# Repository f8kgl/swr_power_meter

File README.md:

# swr_power_meter
Repo of Swr Power Meter project of F8KGL

Afin d'optimiser la qualité de ses communications, l'OM cherche à rendre maximum le transfert de puissance entre l’antenne et l’émetteur (et vice et versa). Ce point de fonctionnement optimum est atteint lorsque les impédances entre l’antenne et l’émetteur sont « adaptées ». Alors, la puissance réfléchie est minimale (idéalement nulle), ou le « SWR » (ou ROS), pour « Standing Wave Ratio » (ou Rapport d’Onde Stationnaire) est proche de (idéalement égal à) 1.

Le « SWR Power Meter F8KGL » (ou Wattmètre/ROSmètre F8KGL) est un dispositif permettant de mesurer la puissance transmise à l’antenne, la puissance réfléchie, et le « SWR ». Il donne ainsi la mesure de la qualité de la chaîne de transmission TRX/Antenne.

Le « SWR Power Meter F8KGL » doit répondre aux besoins suivants :

	-mesurer une puissance de 1W à 500W, avec une précision de 10 %
	-mesurer une puissance dans les 3 bandes radioamateurs HF, VHF, UHF
	-être utilisable par une grande majorité des TRX radioamateurs (50 Ω)
	-être alimenté par une source extérieure en 13,8V, ou par un pack batterie 4x1,5V LR6
	-atténuer le moins possible le signal à transmettre (max 0,2dB)
	-afficher le résultat de la mesure sur un écran LCD (puissance en W, et le SWR sans unité)
	-être solide et robuste pour une utilisation en contest et /P
	-être vendable sous la forme de kit

Ces besoins ont été définis par l’état de l’art technique actuel. En particulier, la technologie moderne appelle l’utilisation de l’électronique numérique le plus souvent possible. C’est pourquoi, l’affichage sur un écran LCD a été choisi. De plus, l’utilisation de moyens informatiques, aussi simples et modestes soient-ils, est préconisé. C’est pourquoi, un microcontrôleur a été choisi pour faire l’interface entre la mesure et l’affichage.

Ce dispositif a été conçu par les OM du club radioamateur « Vauréal Amitié Radio », situé à Vauréal (95), sous l’indicatif F8KGL.
Le projet a été développé par André F0EOS, et Fabrice F4BJH. Portons également à l’attention du lecteur, que l’idée initiale vient de Pierre F1FDD.

1/GPUTILS

1.1/ Désinstaller la version courante de la distribution  
1.2/ Télécharger la version 1.5.0-1 en suivant ce lien :  
https://sourceforge.net/projects/gputils/files/gputils/1.5.0/gputils-1.5.0-1.tar.gz/download  
1.3/ Installation  

	$ tar -xvzf gputils-1.5.0-1.tar.gz

	$ cd gputils-1.5.0-1.tar.gz

	$ ./configure

	$make

	$sudo make install

2/GPSIM  
2.1/ Désinstaller la version courante de la distribution  
2.2/ Télécharger la version 0.31.0 en suivant ce lien :  
https://sourceforge.net/projects/gpsim/files/gpsim/0.31.0/  
2.3/ Installation  

	$tar -xvzf gpsim-0.31.0.tar.gz

	$cd gpsim-0.31.0/

	$./configure

	$make

	$sudo make install

	$sudo /sbin/ldconfig

2.4/Librairie et module GPSIM  
2.4.1/ Création de lien symboliques vers les sources de la librairie, des modules, et le Makefile  

		$cd .../gpsim0.31/modules   #répertoire ou gpsim a été dézippé

		$ ln -s .../swr_power_meter/src/hw/sim/gpsim/lib/Makefile.am

		$ ln -s .../swr_power_meter/src/hw/sim/gpsim/lib/ltc2305.cc

		$ ln -s .../swr_power_meter/src/hw/sim/gpsim/lib/ltc2305.h

		$ ln -s .../swr_power_meter/src/hw/sim/gpsim/lib/swrpowermeterf8kgl_modules.cc

2.4.2/ compiler les fichiers ajoutés  

		$cd .../gpsim0.31/ #répertoire ou gpsim a été dézippé

		$ autoreconf

		$./configure

		$make

		$sudo make install

		$sudo /sbin/ldconfig

3/Utilisation du projet swr_power_meter_f8kgl  
3.1/Télécharger le projet : git clone https://github.com/f8kgl/swr_power_meter  
	$ cd .../prj
	$ make test

	$ cd .../prj
	$ make calibration 

3.2/Calibrator  
    $ cd .../prj  
    $ make calibration_gpsim  

	le make génère le fichier .hex de calibration, à flasher dans l'EEPROM du PIC  

	Usage :
	calibrator [-o][-t][-f][-r][-a adc_value][-p P_in]
	-o : calibration pour le fw opérationnel
	-t : calibration pour le fw de test
	-f : Port FWD
	-r : Port REF
	-a : valeur d'ADC (ADC_m)
	-p : Valeur de puissance en W (Pfwd)

3.3/Simulation  
3.3.1/Modifier le fichier prj/swr_power_meter.stc pour utiliser le fichier de calibration généré à l'étape précédente. Effecteur la mise à jour du projet gpsim :  

   $ cd .../prj
	 $ make update_gpsim

3.3.2/ Lancement de gpsim  
 $ cd .../bin
 $ gpsim -c swr_power_meter.stc

 $ gpsim -c <hardware>.CALIBRATION.stc

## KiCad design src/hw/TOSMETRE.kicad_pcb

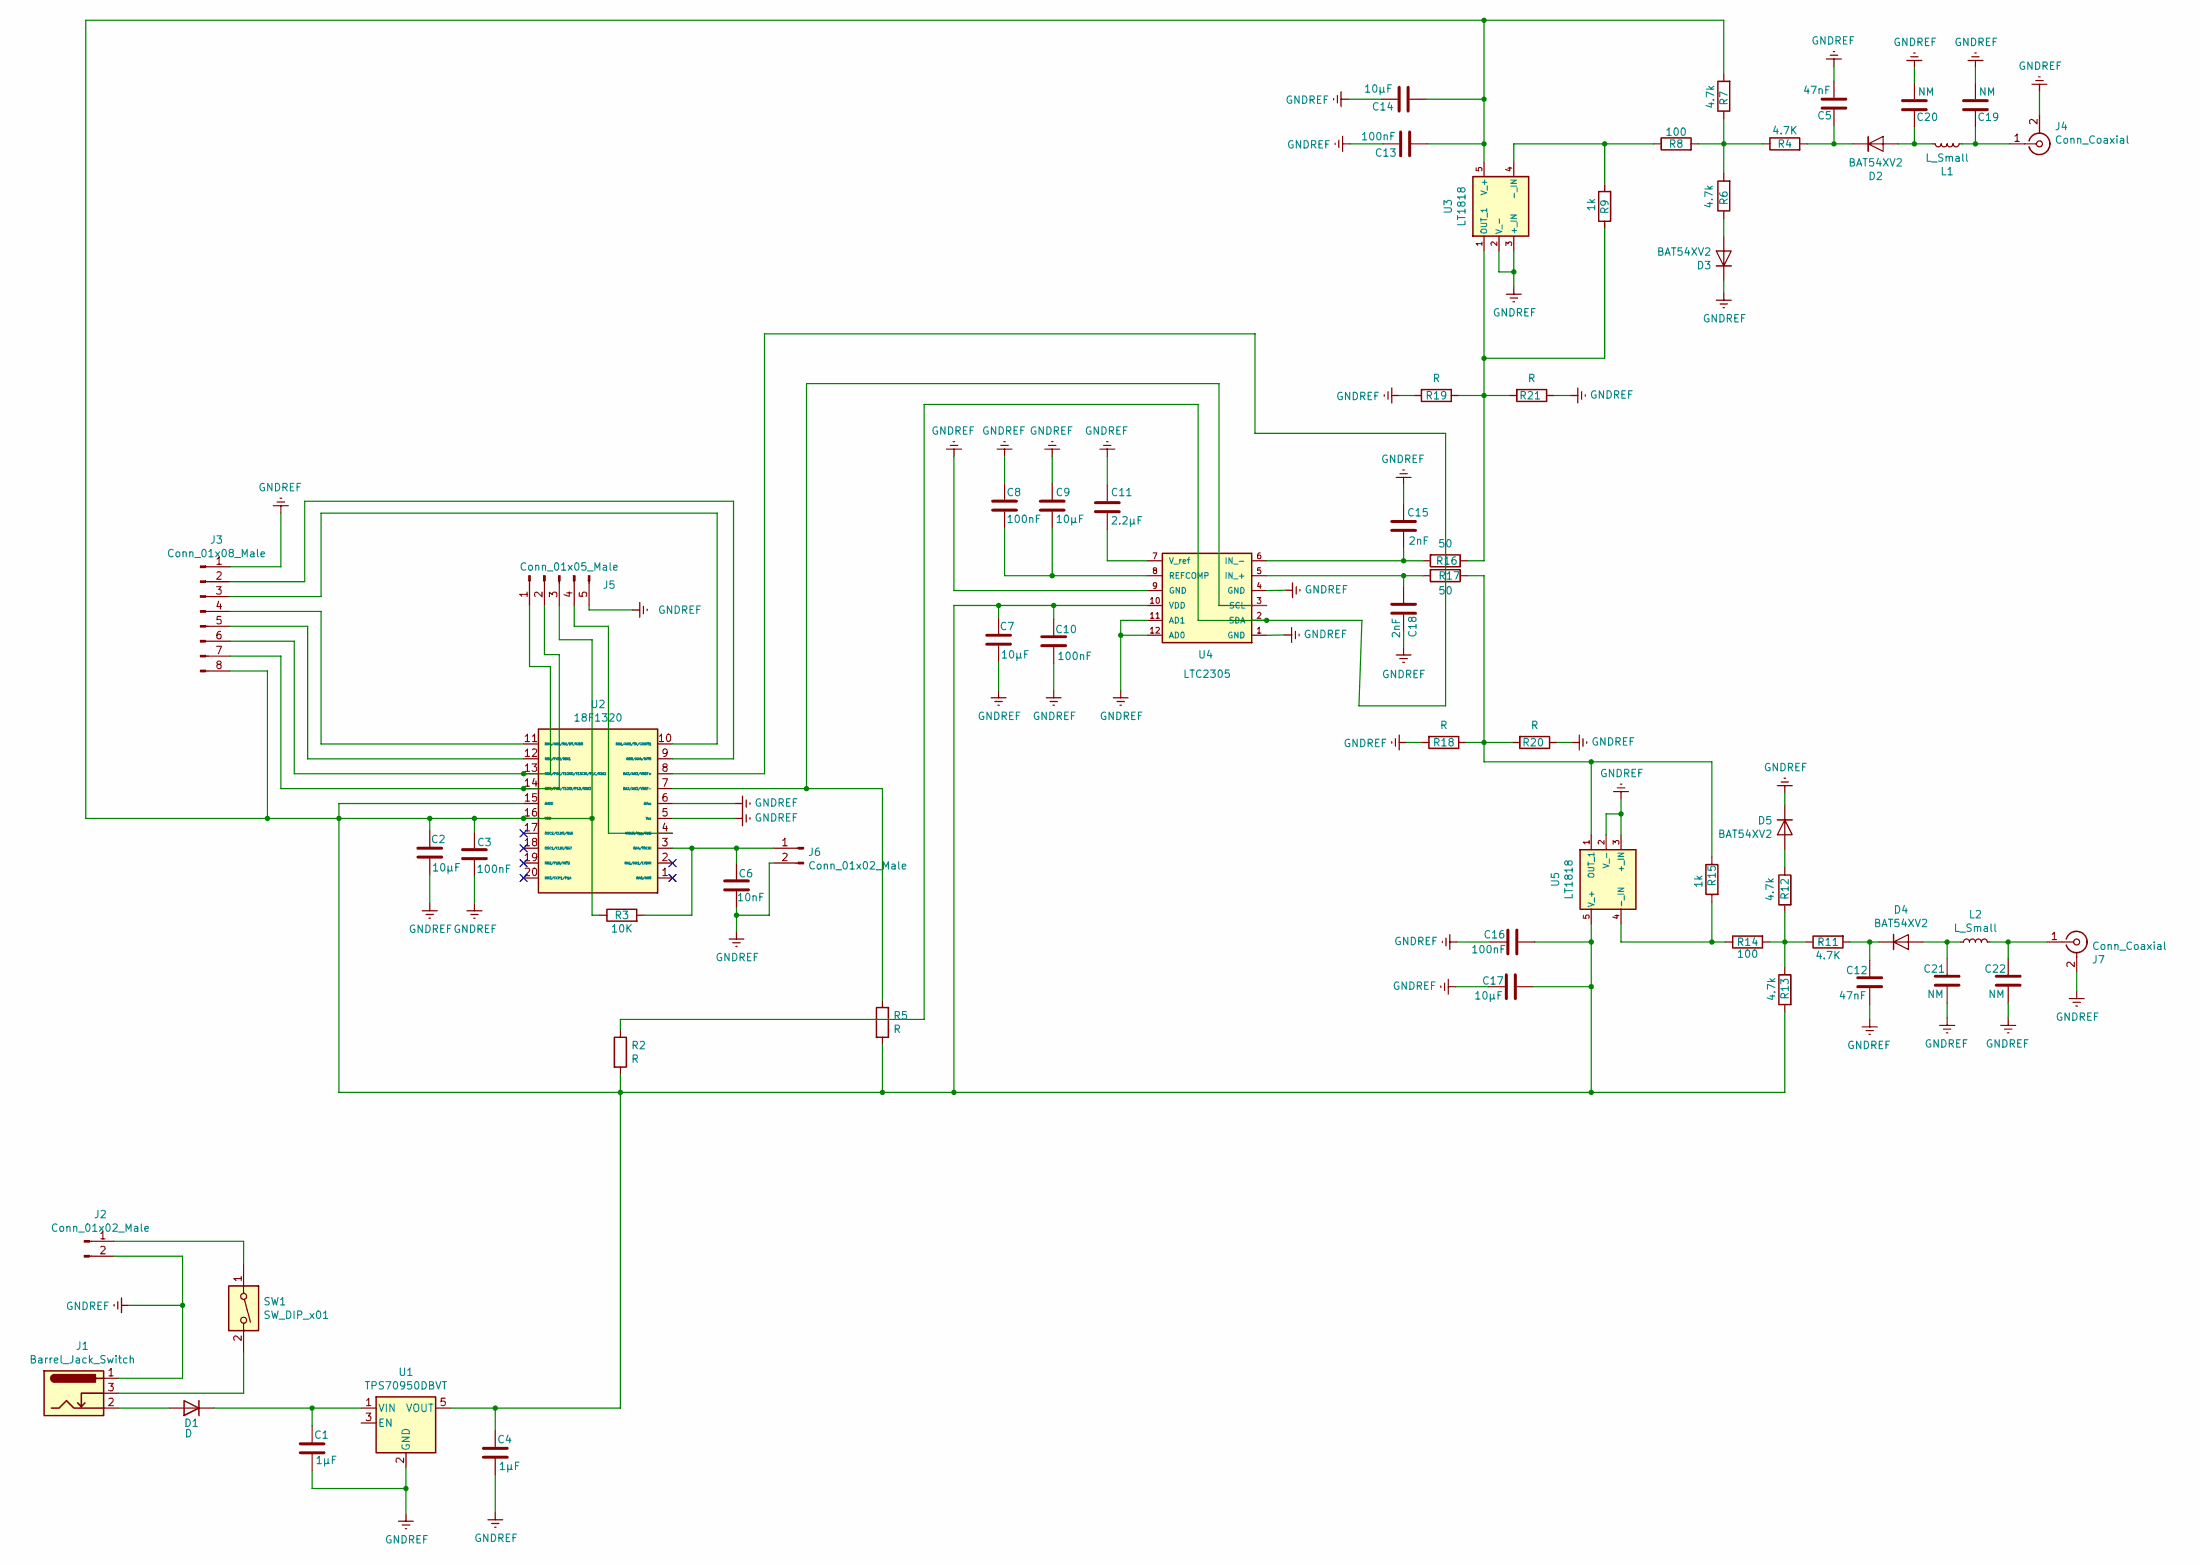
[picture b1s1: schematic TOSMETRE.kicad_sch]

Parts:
C1, C4: 1µF; C_1206_3216Metric
C2, C7, C9, C14, C17: 10µF; C_1206_3216Metric
C3, C8, C10, C13, C16: 100nF; C_1206_3216Metric
C5, C12: 47nF; C_1206_3216Metric
C6: 10nF; C_1206_3216Metric
C11: 2.2µF; C_1206_3216Metric
C15, C18: 2nF; C_1206_3216Metric
C19, C20, C21, C22: NM; C_1206_3216Metric
D1: D; D_1206_3216Metric
D2, D3, D4, D5: BAT54XV2; D_SOD-523
J1: Barrel_Jack_Switch; PinHeader_1x03_P2.54mm_Vertical_SMD_Pin1Left
J2, J6: Conn_01x02_Male; PinHeader_1x02_P2.54mm_Vertical_SMD_Pin1Left
J3: Conn_01x08_Male; PinHeader_1x08_P2.54mm_Vertical_SMD_Pin1Right
J4, J7: Conn_Coaxial; MMCX_Molex_73415-0961_Horizontal_0.8mm-PCB
J5: Conn_01x05_Male; PinHeader_1x05_P2.54mm_Vertical_SMD_Pin1Left
L1, L2: L_Small; R_1206_3216Metric
R2, R5, R18, R19, R20, R21: R; R_1206_3216Metric
R3: 10K; R_1206_3216Metric
R4, R11: 4.7K; R_1206_3216Metric
R6, R7, R12, R13: 4.7k; R_1206_3216Metric
R8, R14: 100; R_1206_3216Metric
R9, R15: 1k; R_1206_3216Metric
R16, R17: 50; R_1206_3216Metric
SW1: SW_DIP_x01; PinHeader_1x02_P1.00mm_Vertical_SMD_Pin1Left
U1: TPS70950DBVT; SOT-23-5
U2: 18F1320; SSOP-20_4.4x6.5mm_P0.65mm
U3, U5: LT1818; TSOT-23-5
U4: LTC2305; MSOP-12_3x4mm_P0.65mm

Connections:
GNDREF: C1.2, C2.1, C3.1, C4.2, C5.2, C6.2, C7.1, C8.1, C9.1, C10.1, C11.1, C12.2, C13.1, C14.1, C15.1, C16.1, C17.1, C18.1, C19.2, C20.2, C21.2, C22.2, D3.1 (K), D5.1 (K), J1.1, J2.2, J3.1, J4.2 (Ext), J5.5, J6.2, J7.2 (Ext), R18.2, R19.2, R20.1, R21.1, U1.2 (GND), U2.5 (Vss), U2.6 (AVss), U3.2 (V_-), U3.3 (+_IN), U4.1 (GND), U4.4 (GND), U4.9 (GND), U4.11 (AD1), U4.12 (AD0), U5.2 (V_-), U5.3 (+_IN)
unnamed: C1.1, D1.1 (K), U1.1 (VIN)
unnamed: C5.1, D2.1 (K), R4.2
unnamed: C6.1, J6.1, R3.2, U2.3 (RA4/T0CKI)
unnamed: C8.2, C9.2, U4.8 (REFCOMP)
unnamed: C2.2, C3.2, C4.1, C7.2, C10.2, C13.2, C14.2, C16.2, C17.2, J3.8, J5.3, R2.2, R3.1, R5.2, R7.2, R13.2, U1.5 (VOUT), U2.15 (AVDD), U2.16 (VDD), U3.5 (V_+), U4.10 (VDD), U5.5 (V_+)
unnamed: C11.2, U4.7 (V_ref)
unnamed: C12.1, D4.1 (K), R11.2
unnamed: C15.2, R16.2, U4.6 (IN_-)
unnamed: C18.2, R17.2, U4.5 (IN_+)
unnamed: C19.1, J4.1 (In), L1.1
unnamed: C20.1, D2.2 (A), L1.2
unnamed: C21.1, D4.2 (A), L2.1
unnamed: C22.1, J7.1 (In), L2.2
unnamed: D1.2 (A), J1.2
unnamed: D3.2 (A), R6.1
unnamed: D5.2 (A), R12.1
unnamed: J1.3, SW1.2
unnamed: J2.1, SW1.1
unnamed: J3.2, U2.9 (RB0/AN4/INT0)
unnamed: J3.3, U2.10 (RB1/AN5/TX/CKINT1)
unnamed: J3.4, U2.11 (RB4/AN6/RX/DT/KIB0)
unnamed: J3.5, U2.12 (RB5/PGM/KBI1)
unnamed: J3.6, J5.1, U2.13 (RB6/PGC/T1OSO/T13CKI/P1C/KBI2)
unnamed: J3.7, J5.2, U2.14 (RB7/PGD/T1OSI/P1D/KBI3)
unnamed: J5.4, U2.4 (MCLR/Vpp/RA5)
unnamed: R2.1, U2.8 (RA3/AN3/VREF+), U4.2 (SDA)
unnamed: R4.1, R6.2, R7.1, R8.2
unnamed: R5.1, U2.7 (RA2/AN2/VREF-), U4.3 (SCL)
unnamed: R8.1, R9.2, U3.4 (-_IN)
unnamed: R11.1, R12.2, R13.1, R14.2
unnamed: R14.1, R15.2, U5.4 (-_IN)
unnamed: R15.1, R17.1, R18.1, R20.2, U5.1 (OUT_1)
unnamed: R9.1, R16.1, R19.1, R21.2, U3.1 (OUT_1)

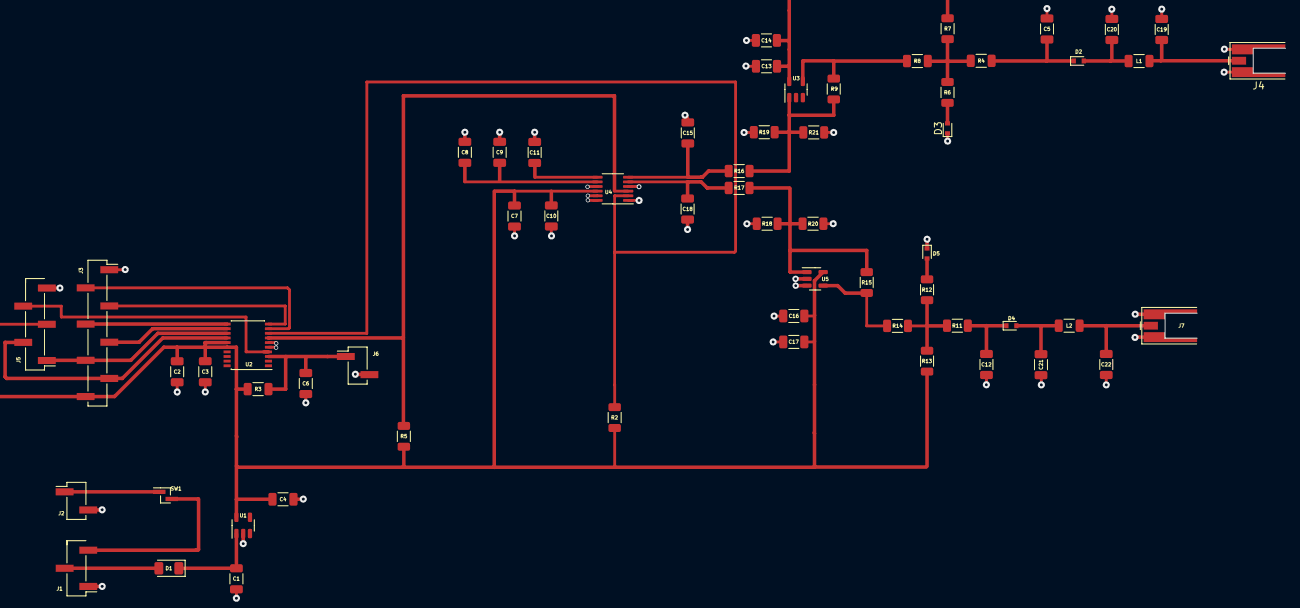
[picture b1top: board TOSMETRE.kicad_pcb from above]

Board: 2 copper layers, 61 parts (0 on the bottom side), 34 nets.

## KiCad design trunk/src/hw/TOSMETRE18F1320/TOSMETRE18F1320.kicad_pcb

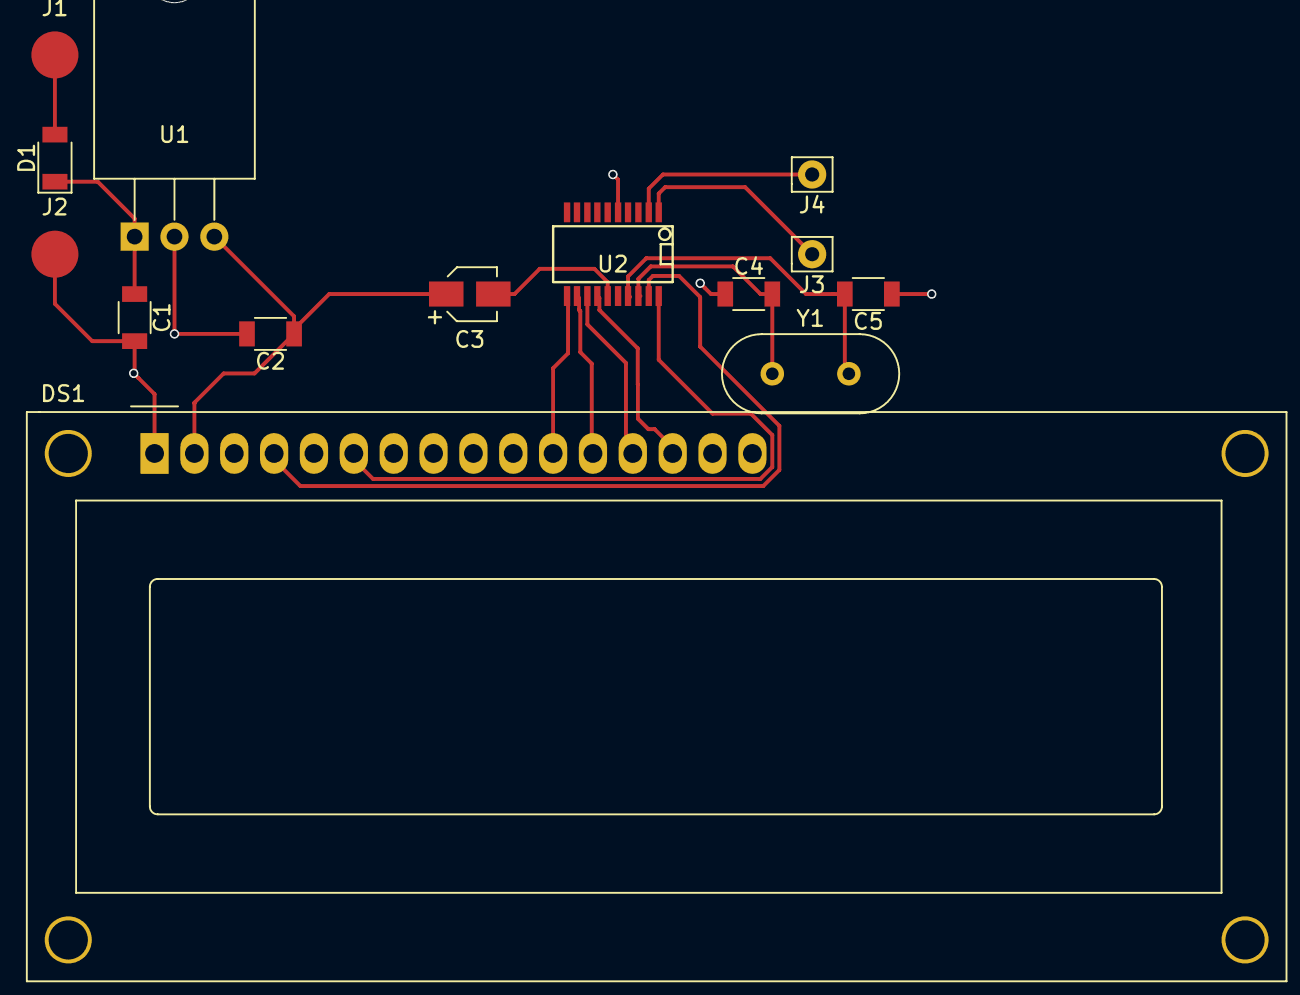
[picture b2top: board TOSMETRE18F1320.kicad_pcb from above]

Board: 2 copper layers, 14 parts (0 on the bottom side), 15 nets.

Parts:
C1, C2, C4, C5: C; C_1206
C3: CP_Small; CP_Elec_3x5.3
D1: D; D_1206
DS1: WC1602A
J1, J2: Conn_01x01_Female; Measurement_Point_Round-SMD-Pad_Big
J3: REF; Pin_d0.9mm_L10.0mm_W2.4mm_FlatFork
J4: FWD; Pin_d0.9mm_L10.0mm_W2.4mm_FlatFork
U1: L7805; TO-220-3_Horizontal
U2: 18F1320_SSOP; SSOP-20
Y1: Crystal; Crystal_HC49-U_Vertical

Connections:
GNDREF: C1.2, C2.2, C4.1, C5.1, DS1.1, J2.1, U1.2, U2.5
unnamed: C1.1, D1.1, U1.1
unnamed: C2.1, C3.1, DS1.2, U1.3
unnamed: C3.2, U2.15, U2.16
unnamed: C4.2, U2.18, Y1.1
unnamed: C5.2, U2.17, Y1.2
unnamed: D1.2, J1.1
unnamed: DS1.4, U2.19
unnamed: DS1.6, U2.20
unnamed: DS1.11, U2.11
unnamed: DS1.12, U2.12
unnamed: DS1.13, U2.13
unnamed: DS1.14, U2.14
unnamed: J3.1, U2.1
unnamed: J4.1, U2.2

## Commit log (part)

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2020-05-28 mise en conformité avec la spec du menu "mesure"
2020-05-28 clignotement LCD en fonction de la valeur de v_calc_port #266 #268 #273
2020-05-28 avec un petit bug d'affichage en moins #275
2020-05-29 ajout init de n #266 factorise #273
2020-05-29 Mettre les capa de découplage du PIC sur VDD #242
    Mise en place des capa de découplage du PIC sur VDD #242
2020-05-30 oups #279
2020-05-30 ben oui...hien, babache #279
2020-05-30 généralisation de la chaine de caractère + revoit l'archi sw du code #279
2020-05-30 un peu de nettoyage
2020-05-31 un tout petit d'archi sw + gestion du bouton avec timeout (dans le cas des rebons d'un bouton) #279
2020-05-31 gestion du bouton cal+ #279
2020-05-31 correction d'un petit bug d'affichage repasse par l'affichage de "FWD G DAC/REF G DAC" systématiquement après un appui sur boutn cal+ #279
2020-06-01 passe la valeur de G dans la FSM #279
2020-06-02 un n-ième retour du bug du PCLATH...#279
2020-06-02 MAJ spec + regen pdf
2020-06-02 spec log #272
2020-06-03 toggle la valeur de n sur port REF #279
2020-06-03 G choisi de manière circulaire #272 mais ne passe pas encore par 0 si "cal-"
2020-06-03 rempli les logs à la bonne adresse en EEP
    le Contenu du champ valeur ne fait que 7 octets (et nons pas 8)
2020-06-03 intégère une trace du timer0 au démarrage #272
2020-06-04 un peu de factorisation
    et affiche la valeur de n dès la rentrée dans le menu de calibration #279
2020-06-04 passe Rdac dans la FSM du LCD #279
2020-06-05 spec du menu "calcul" #188
2020-06-08 modifie les bons registres #271
2020-06-08 position de la partie décimale sur l'écran #271
2020-06-08 applique la nouvelle valeur du DAC à la voie REF aussi #284
2020-06-09 passe la résistance de l'entrée inverseur à 625 ohms #284
2020-06-09 économie de ram et supprime les binaires inutiles
2020-06-09 ajout de l'EEP 256k au breadboard #207
2020-06-09 essai d'optimisation
    essai d'optimisation pour evite les long et tres long ue jonctions entre composants
    mais si on raccourci d'un cote on rallonge de l'autre
    dis moi ce que tu en penses sinon fait faire au projet un retour en arriere
2020-06-10 generation de la table de calibration de TEST #207
2020-06-11 driver EEP externe dans le menu mesure #207
2020-06-16 archi hw revue #263 #249 #230 #226 #216 #215 #95
2020-06-16 510 passe à 625ohms #283
2020-06-16 voir fiche #292
    voir fiche #292
2020-06-17 oubli raccordement C3
    #292
2020-06-19 évite de passer en dessous de R2
    car, pour le coup, R2 est taversé par un le signal de mesure, signal plutôt sensible a priori, et il vaut mieux, dans la mesure du possible, éviter tout couplage avec d'autres signaux...d'autant plus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
2020-06-21 mise en place bouton #274
    SUR U1
    VERIFIER AVSS ET VSS
    mise en place des bouton sur RA0-RA1- et RA4
2021-02-12 Create SWR_POWER_METER_F8KGL_Tests.fodt
    #219 #293
2021-02-12 Update SWR_POWER_METER_F8KGL_Tests.fodt
    Ajout de test #293
2021-02-12 ajout d'un pont diviseur de tension
    #260 ajout d'un pont de résistance pour les tests sur version proto p23 et 28
2021-02-13 #303
    Ajout REF et FWD
2021-02-15 rotation de texte
    #303
2021-02-16 MAJ principe de calibration #146
2021-02-16 génération from scratch dans les docs
    documente la génération from scratch (à reporter aussi dans la doc d'implémentation) #313
    et du coup, ajoute la génération de la table dans la règle "all"
2021-02-17 #307
    Mise a jour des empreintes pour le schema
2021-02-17 Update SWR_POWER_METER_F8KGL_Tests.fodt
    #293
2021-02-17 #299
    #299 deplacement capa de decouplage
2021-02-17 #301
    Modification valeur R1 et R4 valent 510 ohms (pas 625)
2021-02-17 #301
    Rajout commentaire résistance test ADC1 sur resistance R6 et R5
2021-02-17 ah y est, t'es content là mainteant #?$*!§
2021-02-18 #320
    Peux tu verifier si le remplacement du 7805 est ok
    Dans ce cas je le supprimerai pour ne laisser que le tps709
2021-02-18 correction doc
    corrige la connection GND du LTC2305 dans les specs + regen pdf #320
2021-02-18 #320
    suppression des capa sur la borne 1 {GND) du LTC2305
2021-02-18 #315
    pour mise a jour ds composants sur pc pro
    pas de modif particuliere
    Accessoirement tuto pour Post pour Francois
2021-02-19 #308
    mise en place de l'interupteur
    Fab peut tu valider la modif afin de supprimer la partie alimentation a base du 7805 STP
2021-02-22 Update TOSMETRE.erc
    #325
2021-02-22 #315
    Ajout de Diodes D4 et D5 sur la " double" alimentation
2021-02-23 #315
    déplacement diode esthétique
2021-02-23 Update brouillon_spec_V1.0.fodt
    #264
2021-02-23 #318
    ok fait
2021-02-23 revoit entièrement la spec suite à la notion de version d'étude en V0.8 #188
2021-02-23 refonte de l'étude #326
2021-02-24 test de conformité par rapport aux fonctionnalités HW attendues + ajout d'un test sur le K de la diode + ajout d'un test sans AOP #326
2021-02-24 clarifie
    #326
2021-02-24 #308
    définition de l'empreinte de J6 avec détrompeur pour PCB avec génération de la net-liste
2021-02-24 ajout d'un § sur la T° + regen pdf #328
2021-02-24 codage de la calibration de la puissance par table #328
2021-02-25 BJH doit retourner à l'école
    pour faire des multiplications #332
2021-02-25 ajout de 2 Tests de sensibilité
    sur la carte d'étude #328
2021-02-25 supprime toute trace de l'EEP dans les spec #331
2021-02-25 ajout d'un circuit d'adapation d'impédance aux spec #333
2021-02-26 étude d'un circuit de coompensation en T° #328 + ajout d'un test de stabilité #328 + spec #327
2021-02-26 étude aop
    + test + divers calcul excel
2021-03-01 Update SWR_POWER_METER_F8KGL_etude.fodt
    étude du calcul de la tension calibrée : calcul de la partie entière et décimale ramenée en entrée de l'AOP #338
2021-03-02 nbeuses modifs
    modif AOP + suppression AD5175 + étude remontée de mesure en W (et dBm) + ajout d'une feuille de calcul pour tout cela #339
2021-03-02 #302
    ajout pont diviseur mais je ne suis pas bien sur d'avoir compris
2021-03-02 #324 supprimer u4 et u7
    fait
2021-03-02 supprime le driver EEP #336 ajout d'une règle de maj du proj gpsim dans le makefile #345
2021-03-02 #324
    petit peu de nettoyage :
    C16, C17, C6, C11
2021-03-03 # modif patte out a la masse
    si c'est ok il reste le deuxieme a faire
2021-03-03 #343
    RAJOUT FILS MANQUANT
2021-03-03 étude de la chaine rf
    calibration : §5.3.2 #344
    puissance en dBm #347
    #340 #341
2021-03-03 #333 adaptation 50 ohms
2021-03-03 # modif libelle bouton freq
2021-03-04 clarification des specs pour les boutons
    suppression des boutons cal+ et cal-
    +ajout d'un filtre anti-rebond et pull up sur le bouton bande #274
2021-03-04 #350
2021-03-04 conversion en mV
    specs #353
2021-03-04 connecteur de programmation #306
    + oups #315
2021-03-05 #274 boutons calibrations supprimes
    pullup sur bouton bande
2021-03-05 spec calcul en dBm
    1ère mouture #347
2021-03-05 #357
    Grosse modification pour "coller" avec la grille
    Grosse aération du schéma
    Optimisation peut être a prévoir
    Attention nouvelle reference et appelation des composants
2021-03-06 adapte les specs aussi du coup #353
2021-03-06 #302 #307
    Modif condensateur C18
    Ajout pont diviseurs
    du coup de ne sais pas s'il faut laisser le C ou le retirer ?
2021-03-06 commence le transfère des fonctions de conversion vers CALC #359
2021-03-07 #357
    DEPLACEMENT PARTI REF
2021-03-08 mise ne place d'un pointeur pour la conversion BCD #362
2021-03-08 compil
    #363
2021-03-08 ajout d'un log
    timer SAMPLE #359
2021-03-08 pourquoi faire simple
    quand on peut compliqué #359
2021-03-08 modif spec suite à derniers dev sw
2021-03-08 quad l'adresse des log est à 0xFF, la prochaine adresse d'écriture n'est pas 0x00 mais 0x20. On détecte le passage 0xFF -> 0x00 par le bit carry du registre status #373
2021-03-09 début de calcul en mV
    mise en en place de la nouvelle version de la conversion BCD (optimisée en RAM+résultat sur 2 octets) #362 #359 #353
2021-03-09 gros oups qd même...#362 #359 #353
2021-03-09 ajoute de la conversion bcd et ascii
2021-03-10 un peu d'optmisation
    de code et de RAM (tout ça pour 1 octet...)
2021-03-11 étude et spec du calcul de P en dBm
    #347
2021-03-11 affichage de la tension en mV #375 #362 #359 #353 +compil +modif Vref = 0,3V dans gpsim #378
2021-03-12 mise en oeuvre d'un octet en EEP pour activation d'un niveau de trace en fonction du tag
    #380
2021-03-12 c'est la crise, faut faire des économies #359
2021-03-12 tests gputils et gpsim #360
2021-03-12 ajout tests des log #360
2021-03-15 ahhh...l'octet de config de trace est en 0x1F
    #380
2021-03-15 tstfsz ne fonctionne que sur des files + gestion correcte du bit zero du regsitre de status #3810
2021-03-16 introduit la notion de TAG et d'ID_LOG #380
2021-03-16 début de mise en oeuvre de la table 10*log(ADC)
    #347
2021-03-16 tu es trop lent petit scarabé :-p +IF 0 d'une partie du menu puissance_dBm pour éviter le plantage
2021-03-17 génération de la table de 10*log(ADC) #347
2021-03-17 gros travail d'optimisation #384 #347 #359
2021-03-17 Ahhh...ça fait plaisir de se séparer de INDF0 et INDF1 !!! Enfin !!! #359
2021-03-18 calibrator #347
2021-03-18 calcul de P en dBm #347
2021-03-19 replace les valeurs de calibration avec R1=R2=1 ohms, pour être cohérent avec l'état actuel de la simu #347
2021-03-22 etude et spec du calcul de P en W #390
2021-03-22 sort _v_calc_bcd_count de sa fonction pour la rendre paramètrable +ajout de Kconv(nW) en EEPROM #390
2021-03-23 donne accès aux paramètres de calibration
    en ligne de commande #390
2021-03-23 calcul de P en W #390
2021-03-25 pour optmisation RAM
    séparation TEST/CALIBRATION/OPERATIONNEL #359
2021-03-29 #304
    implentation composants
2021-03-30 gagne 4ko de code pour le SWR_POWER_METER #359
2021-03-31 déjà, faut lui donner des données de calibration hein #347
2021-04-01 compléments sur les tests manuels et ajouts de commentaires sur les tests auto #360
2021-04-01 ajout d'un test pour vérifier le temps de conversion ADC #180
2021-04-01 #305
    pour validation
    Pise 1mm
    via diametre 1,4 et percage de 0,6
2021-04-01 remet la puissance en dBm sur la voie FWD de manière correcte #347
2021-04-02 #305
    suite du routage
2021-04-04 nettoie #347
2021-04-04 #305
    MODIFICATION EMPREINTE J3 J5 ET J2
2021-04-05 oups
2021-04-05 spécifie le calibrator du fw de test #344
2021-04-06 #304
    OUPS DES PETIT OUBLI
2021-04-13 nom de fichier incorrecte #398
2021-04-18 Mise à jour des how to #296
2021-04-18 ambiguité #398
2021-04-19 #305
    MODIFICATION CIRCUIT
    RAPPROCHEMENT DES COMPOSANTS SUR PISTES
    RAJOUT PLAN DE MASSE
2021-11-06 #305
    rajout non connection sur U2 borne 1 et 2
2022-02-07 #146 #188 supprime toutes traces de V1.0 et au dessus (pour pouvoir passer aux dev des tests) spécifie le programmateur (câble + connecteur)
2022-04-09 #173
    Mise a jour suite a la version kicad 6
2022-05-03 #406
    pour verification 18F1320 sans pave
2022-05-04 #406
    DEBUT DU ROUTAGE
2022-05-06 #406
    Modification des pistes de 0.25 a 0.40
    modification des VIa de 0.6 a 1
    "compactage "du pcb
    envoie depuis le reseau WIFI du TGV arrivant en gare de nimes
2022-05-13 #406
    PB termine
    Nouvelle appleation suite a mauvaise manip (GRRRR) desole
    Voir si on peux pas changer R1et R2 pour eviter qu'une piste passe dessous
2022-05-16 #406
    re routage en cours suite a plantage
2022-05-17 #406
    routage terminer
    attente de validation
2022-05-20 #412
    via au plus pres des composants
2022-05-20 #410
    Modif Schema et routage sur J5 a valider par grand MANITOU
2022-05-21 #412
    OUBLIE DE MASSE SUR CERTAIN COMPOSANTS
    VERIFIER LES VIA DE gnd CERTAIN SONT PLUS PETIT A CAUSE DU DRC
2022-05-23 #264 ajout des parties fw de calibration et opérationnel
2022-05-24 #417
    RACCORDEMENT BORNE 8 DE u2
    Mauvaise connection dans le schema donc la netliste ne le voyait pas
    rectif faite
